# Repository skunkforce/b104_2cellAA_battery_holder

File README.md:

# edgy_board number b104
This design is part of the [edgy board project](https://github.com/skunkforce/edgy_boards).

# getting started
This repository uses submodules. After cloning use the command 

```$ git submodule update --init --recursive```

to pull the submodules before opening the project with kicad. 

# Tests
Tests can be found in [TESTS.md](TESTS.md)

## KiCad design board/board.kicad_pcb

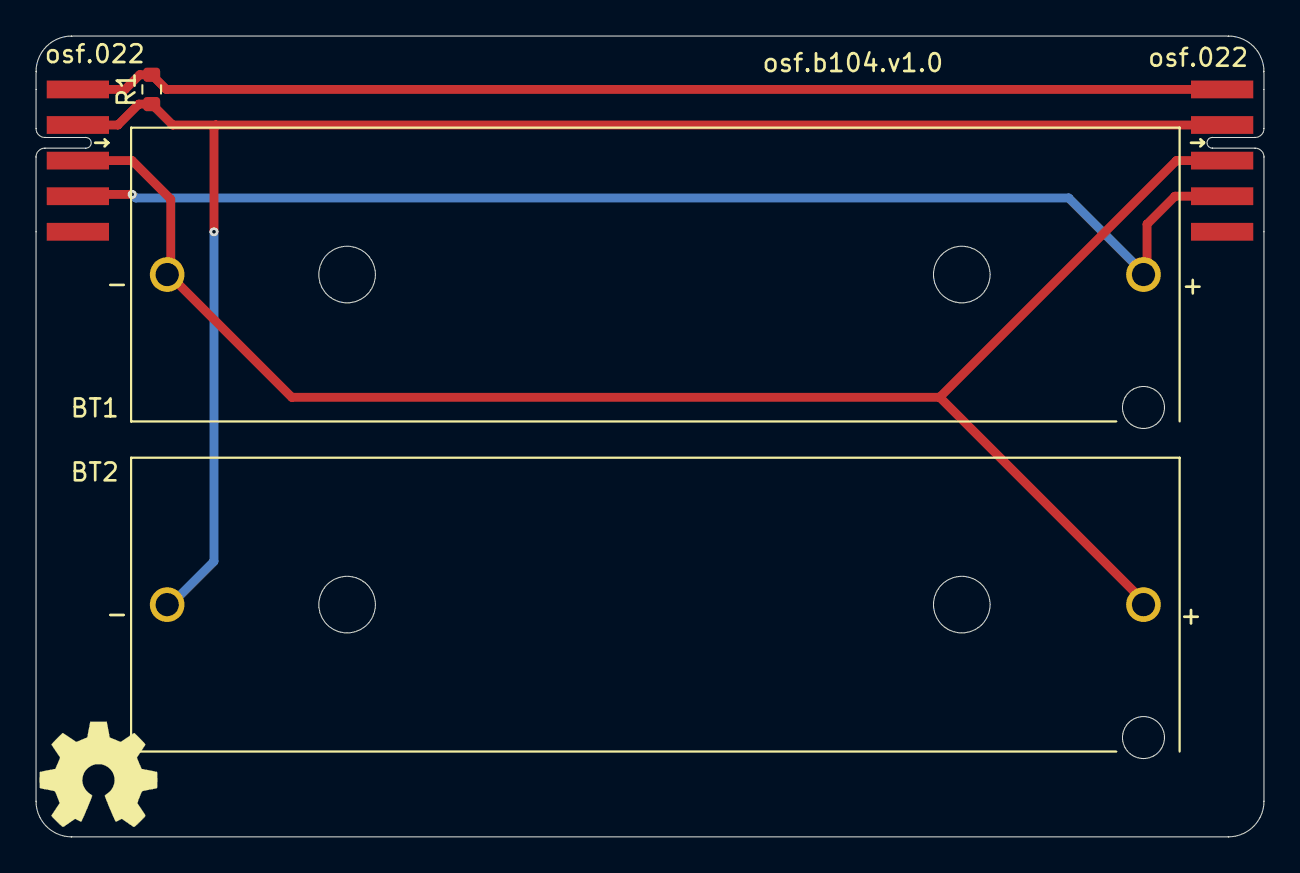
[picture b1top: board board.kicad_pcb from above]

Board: 2 copper layers, 69.0 x 45.0 mm, 6 parts (0 on the bottom side), 4 nets.

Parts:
BT1, BT2: BHAA-3-G; BAT_BHAA-3-G
J1: 022_battery_cells; on_edge_2x05_device
J2: 022_battery_cells; on_edge_2x05_host
LOGO1: Logo_Open_Hardware_Small; OSHW-Symbol_6.7x6mm_SilkScreen
R1: 0R; R_0603_1608Metric

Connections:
/implementation/C1+C2-: BT1.-, BT2.+, J1.3 (C1+C2-), J2.3 (C1+C2-)
/implementation/C1-: BT2.-, J1.2 (C1-), J2.2 (C1-), R1.1
/implementation/C2+: BT1.+, J1.4 (C2+C3-), J2.4 (C2+C3-)
GND: J1.1 (GND), J2.1 (GND), R1.2

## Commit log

2023-03-08 initial
